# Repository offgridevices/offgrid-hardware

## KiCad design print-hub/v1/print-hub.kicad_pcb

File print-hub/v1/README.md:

# Print Hub — v1

**Five switched USB ports for a resin printer's accessories**, controlled
by the print server. The exhaust fan, the light and the air filters plug
into the board; when a print starts, the server tells the board which ports
to switch on, and later which to switch off (and when). Each port measures
its own current, limits it, and can never put more than 5.4 V on a device.
The board talks Wi-Fi, and has a USB-C port for the server too.

> **Status: designed, not yet built.** Routed 4-layer board, 86 × 50 mm,
> every track corner at 45 degrees, KiCad 10 DRC 0 errors, 0 warnings,
> 0 unconnected; every gate, design check and simulation in `TESTS.md`
> passes, the board's heat in its closed case included; firmware builds and
> its logic passes its tests on the host. Nothing has been measured on hardware: order a few,
> bring one up (below), then use it.

## This revision

| | |
|---|---|
| Revision | **v1** (product: [`../README.md`](../README.md)) |
| Status | designed, not yet built |
| Tests and simulations | [`TESTS.md`](TESTS.md): every one with its v1 result |
| Trade-offs | [`docs/decisions.md`](docs/decisions.md) |
| Parts, stock, second sources | [`docs/parts.md`](docs/parts.md) (read 17 Oct 2026) |
| Toolchain | KiCad 10.0.6 (pinned image, `tools/Dockerfile`), Freerouting 1.9.0, ngspice |
| Firmware | ESP32-S3, Arduino core 3.3.12 (pioarduino 55.03.312-1), `firmware/` |
| Brand | OffGrid v3.2.2 ([`docs/brand.md`](../../docs/brand.md)) |

## Requirements

As the owner set them, and where v1 stands.

| Requirement | v1 |
|---|---|
| One USB-ish box behind the printer that switches the accessories automatically | ✅ 5 switched USB-A ports, commands from the print server |
| 4 ports, 5 if possible | ✅ 5 |
| Controlled from the Dell over USB, or Wi-Fi | ✅ both: Wi-Fi (HTTP, `printhub.local`) and USB-C to the server, same commands |
| Easy to configure from an SSH session ("port 1 is the fan") | ✅ `printhub name 1 fan`; names, limits and priorities live on the board |
| Never burns anything out | ✅ each port's switch limits at 1.92-2.20 A and shuts down when hot; a 1.5 A software limit per port; 5.4 V output clamp; 3 A for all ports together, and a thermistor by the buck: the firmware turns ports down before any part passes its rating (`sim/thermal/board_heat.md`) |
| Never browns out the other electronics | ✅ a short on one port leaves the others above 4.75 V (`sim/port_events.md`); the firmware keeps the total under what the charger offers; the server's USB never feeds a port |
| Knows how much power it can give | ✅ reads the charger's USB-PD contract and budgets the ports from it |
| Powered from the Dell alone if possible | ⚠️ the logic yes; the accessories need about 15 W, three times what a PC USB port gives, so the ports need a USB-C charger (20 W or more) — `docs/decisions.md` |
| Relay or something reliable | ✅ solid-state USB power switches (TI TPS25200): silent, no wear |
| Not too big, not too expensive | ✅ 86 × 50 mm (under 100 mm a side: JLCPCB's $8 price for five 4-layer boards); about $11.50 of parts a board plus JLCPCB's fees (see *Ordering*) |
| Order fully assembled | ✅ JLCPCB: every part from its catalogue, BOM and CPL in `production/` |
| A 3D-printable enclosure the board screws into | ✅ `mechanical/enclosure/` |

## Next steps

1. **Order 2-5 boards** (see *Ordering*). Re-read stock first
   (`python3 tools/lcsc.py C2913198 ...`): `docs/parts.md` is dated.
2. **Print the enclosure** (`mechanical/enclosure/README.md`) and buy the
   screws, a USB-C PD charger (20 W or more) and two USB-C cables.
3. **Bring one up** (below): flash, join Wi-Fi, name the ports, load-test
   each port against a USB meter.
4. **Wire it into the print server's start/end hooks**
   (`host/examples/print-hooks.sh`).
5. **Record what the board measured** in `TESTS.md` (the hardware rows).

---

## What's on the board

- **POWER IN (USB-C, back left).** A Hynetek HUSB238 asks the charger for
  9 V over USB-PD; a Silergy SY8368A buck makes 5.16 V for the ports (rated
  5 A; the firmware allows 3 A, what the closed case can shed). A 15 V TVS
  on the input, and a thermistor between the buck and its inductor, the
  hottest corner.
- **DATA (USB-C, back middle).** Straight to the ESP32-S3's own USB (serial
  console and flashing), ESD-protected. It powers the logic, never the ports.
- **ESP32-S3-WROOM-1 (back right)**, its antenna at the board's edge with no
  copper under it. RESET and BOOT buttons and the status LED beside it.
- **Five port blocks (front)**, one per USB-A: a TI TPS25200 switch (current
  limit 2.07 A typical, soft start, fault line, 5.4 V output clamp), a
  20 mOhm shunt and a TI INA180A2 amplifier (1 V per A into the ESP32's
  ADC), and an RGB LED. D+ and D- are joined (a USB charging port), so
  devices may draw 1.5 A.
- **LEDs**: one per port (green on, blue about to come on, blinking red
  tripped, amber off for lack of power or heat) and a status LED (green on
  Wi-Fi, blinking blue in setup mode, blinking red with no USB-PD charger,
  amber while heat is turning the ports down, fast red blink when heat has
  switched them all off).
- **Test pads**: UART TX/RX and ground (boot log), and the 5 V rail.

| | |
|---|---|
| Size | 86 × 50 mm, 1.6 mm, square corners, 2 × M3 holes at (-39.5, -21.5) and (7.0, -2.5) mm from the centre (the USB-A ports hold the front edge in the case) |
| PCB | 4 layers (F signals, In1 ground, In2 5 V plane, B signals), 1 oz outer, 0.15 mm track and gap, 0.6 / 0.3 mm vias, every track corner 45 degrees or less: JLCPCB's standard tier |
| Input | USB-C PD, 9 V (asks for 9 V; 5 V-only chargers run the logic but no ports) |
| Ports | 5 × USB-A 17 mm apart, 5.16 V, 1.5 A each (the USB-A receptacles' rating; less if set), 3 A in total (2.7 A on a plain 20 W charger), less if the board gets hot |
| Control | Wi-Fi 2.4 GHz (HTTP API, mDNS `printhub.local`), USB serial |

## Ordering (JLCPCB)

From `production/`:

- **Gerbers**: `print-hub-gerbers.zip`.
- **4 layers, 1.6 mm, 1 oz outer / 0.5 oz inner** (JLC04161H-7628).
- **Green solder mask, white silkscreen, lead-free HASL**: the cheapest
  build. Black mask adds $8 and ENIG $17 per order of five (live quotes,
  18 Oct 2026); either works if wanted.
- No special options: no via-in-pad, no fine-line, no impedance control.
- **Assembly: top side only**: upload `print-hub-bom-jlcpcb.csv` and
  `print-hub-cpl-jlcpcb.csv`. Try "Economic PCBA" first: with a green mask
  the board qualifies, and JLCPCB's capability page now lists through-hole
  parts (the five USB-A) for it, which saves about $40 of setup. If the
  quote refuses, use "Standard PCBA".
- **Check before you pay**, in JLCPCB's placement preview: the pin-1 corner
  of the six WS2812B LEDs, the bands of the two B5819W diodes (D2, D3) and
  of the SMAJ15A (D1), and that the USB-C and USB-A connectors face off the
  board edge.

PCBWay: `print-hub-bom-pcbway.csv` carries manufacturer part numbers and
LCSC numbers.

**Cost, roughly** (18 Oct 2026, 5 boards): the PCB $8 (4 layers, green,
HASL, under 100 × 100 mm; the first 104 × 66 mm layout quoted $29); parts
about $11.50 a board; 14 extended + 2 preferred-extended part types at about
$3 each, so about $45 of setup fees per order; plus assembly setup and the
through-hole soldering. Ten boards halve the fees per board. Read the quote.

**Also buy:** a USB-C PD charger, 20 W or more (any phone or laptop one);
a USB-C cable for power and a USB-C to USB-A (or C) cable to the server;
M3 screws and inserts for the enclosure (its README has the list).

## Bring-up

1. **Before power**: look for solder bridges on the USB-C pins and the ESP32
   module.
2. **DATA only (no charger)**: plug DATA into the print server. The status
   LED blinks red (no charger, which is expected). `ls /dev/ttyACM*` shows
   the board.
3. **Flash the firmware** from the server (once; later updates can go over
   Wi-Fi):
   ```
   pip install esptool
   esptool --chip esp32s3 --port /dev/ttyACM0 write-flash 0x0 firmware/release/printhub-v1.1.0-factory.bin
   ```
   If esptool cannot connect: hold BOOT, press and release RESET, release
   BOOT, and run it again. Or build and flash from source:
   `cd firmware && pio run -t upload`.
4. **Install the command** on the server: `sudo cp host/printhub.py
   /usr/local/bin/printhub` (Python 3, nothing else to install).
5. **Join Wi-Fi** over the cable: `printhub wifi "Network name" "password"`,
   then `printhub status` shows its address. Optionally `printhub token
   SECRET` and `export PRINTHUB_TOKEN=SECRET` on the server.
6. **Plug in the charger** (POWER IN): the status LED turns green, and
   `printhub status` shows `9V ... USB-PD` and how many mA the ports may draw.
7. **Name the ports and test each one** with a USB load or a USB meter:
   ```
   printhub name 1 fan
   printhub name 2 light
   printhub name 3 filter1
   printhub name 4 filter2
   printhub priority fan 1
   printhub on fan          # LED goes green; status shows the current
   printhub off fan
   ```
   Check each port's reading against the meter, and that 5 V reaches the
   device (4.9-5.2 V).
8. **Hook it to the print server** (`host/examples/print-hooks.sh`):
   `printhub on fan light filter1 filter2` when a print starts;
   `printhub off fan after 15m`, `printhub off light after 3m`,
   `printhub off filter1 filter2 after 30m` when it ends. The timers run
   on the board, so they happen even if the server restarts.

The air filters: their own power button has to be pressed for them to run,
so wire it permanently on (the plan), and switching the port then decides
whether they run on charge.

## Controlling it

Home Assistant: [`docs/home-assistant.md`](docs/home-assistant.md) has the
switches and sensors ready to paste.

Over Wi-Fi: `http://printhub.local/` is a small page with the five ports
and on/off buttons. Scripts and AI agents use the same commands as the CLI,
by `printhub ...` or `POST /api/cmd` with the command as the body, and get
JSON back (`firmware/lib/hub/src/cmd.h` lists every command):

```
printhub status                     printhub on fan light [for 10m]
printhub off all                    printhub off fan after 15m
printhub name 3 filter1             printhub limit filter1 1200
printhub priority fan 1             printhub boot light on
printhub --json status              printhub ota http://server/printhub.bin
```

## Limits

- **The ports need a USB-PD charger that offers 9 V** (practically every
  USB-C charger of 18 W or more). A 5 V-only charger runs the board but no
  ports; the firmware says so. Budget by charger: 20 W gives the ports
  2.7-3.0 A, 27 W and up the full 3 A (`sim/power_budget.md`).
- **1.5 A per port at most** (the USB-A receptacles' rating; the switch's own limit is
  1.92-2.20 A); **3 A in total**: what the closed case sheds in a 35 C room
  with every part inside its rating (`sim/thermal/board_heat.md`). The
  typical load, fan + light + two filters charging, is about 2.65 A.
- **Heat**: hotter than that (a hotter room, the case in the sun, its feet or
  vents blocked), the thermistor by the buck turns the ports down from
  74 C on the board (down to 1 A by 77 C), lowest priority first, and switches them all off at
  80 C until the board is back under 70 C. `printhub status` shows the
  board's temperature.
- **2.4 GHz Wi-Fi only.** Keep metal and the screws away from the antenna
  corner; the enclosure does.
- **Power-only USB ports**: no data reaches the accessories.
- **Not measured on hardware yet**: the buck's feed-forward capacitor (22 pF)
  and the 1.5 A software limit are first guesses to confirm on the bench.

## Build

Everything runs in the pinned toolchain image. Build it once (the
Dockerfile's header says how), then from this folder:

```
tools/kd python3 src/make.py              # gates and every output from the committed board
tools/kd python3 src/make.py --artwork    # lay the silkscreen out again first
tools/kd python3 src/make.py --reroute    # place and route from scratch, then everything
tools/kd python3 src/verify.py            # design checks, writes VERIFICATION.md
tools/kd python3 sim/port_events.py       # ngspice: ports switching on, a port shorted
tools/kd python3 sim/thermal/board_heat.py  # the board's heat in its case (~5 min)
python3 sim/power_budget.py               # the power chain from the datasheets
make -C firmware/test                     # firmware logic, on the host
python3 host/test_printhub.py             # the CLI against a fake board
cd firmware && pio run                    # the firmware
```

The committed `print-hub.kicad_pcb` is the design of record: CI (`ci /
print-hub-v1`) rebuilds the artwork and every fab file from it and fails
if they differ from what is committed. `make.py --reroute` reproduces it
from `src/` (placement, power copper and Freerouting are deterministic).

| To change | Edit | Then run |
|---|---|---|
| A part number (same footprint) | `src/parts.py` | `make.py` |
| Labels, logo | `src/silk.py` | `make.py --artwork` |
| Connections, placement, power copper | `src/circuit.py`, `src/layout.py`, `src/power.py` | a new revision: copy to `v2/`, `make.py --reroute` |
| Firmware pins or scaling | `firmware/src/board.h` (must match `src/circuit.py`) | `verify.py` |

## Files

```
README.md               this file
TESTS.md                every test and simulation with its v1 result
VERIFICATION.md         design checks (src/verify.py)
print-hub.kicad_pcb     the routed board (design of record), .kicad_pro, .kicad_dru
production/             Gerber zip, BOM and CPL (JLCPCB, PCBWay), netlist, assembly PDF
images/                 renders and the silkscreen read back from the Gerbers
mechanical/             STEP of the assembled board (zipped); enclosure/
firmware/               ESP32-S3 firmware (PlatformIO), host tests, ready-to-flash images
host/                   printhub command for the print server, its tests, example hooks
docs/                   decisions, parts (dated), Home Assistant
sim/                    power-chain analysis, ngspice port events, the board's heat in its case
src/                    the generator: circuit, footprints, placement, power copper, routing, artwork, checks
ph.pretty/, ph.3dshapes/  this board's footprints and their 3D models
fonts/                  brand fonts for the silkscreen (OFL)
tools/                  pinned toolchain (Docker), CI output check, JLCPCB stock lookup
```

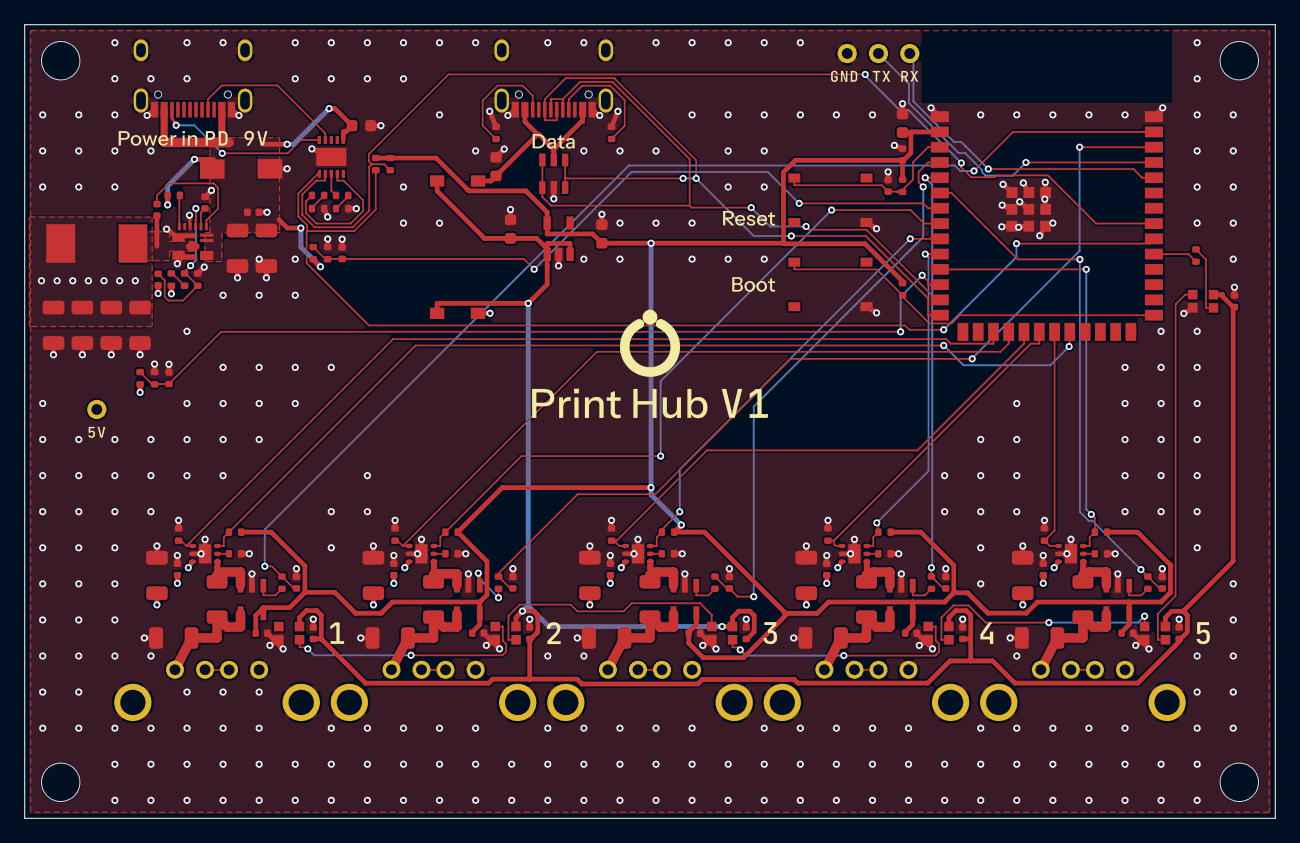
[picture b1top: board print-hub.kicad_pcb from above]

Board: 4 copper layers, 104.0 x 66.0 mm, 136 parts (0 on the bottom side), 77 nets.

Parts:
C1: 1uF; C_0603_1608Metric
C2, C3: 10uF; C_1206_3216Metric
C4, C5, C12, C13, C18, C20, C101, C103, C104, C106, C201, C203, C204, C206, C301, C303, C304, C306, C401, C403, C404, C406, C501, C503, C504, C506: 100nF; C_0402_1005Metric
C6, C19: 1uF; C_0402_1005Metric
C7: 22pF; C_0402_1005Metric
C8, C9, C10, C11, C102, C105, C202, C205, C302, C305, C402, C405, C502, C505: 22uF; C_1206_3216Metric
C14, C15, C16: 10uF; C_0603_1608Metric
C17: 22uF; C_0603_1608Metric
D1: SMAJ15A; SMA_L4.3-W2.6-LS5.0-RD
D2, D3: B5819W; SOD-123_L2.7-W1.6-LS3.7-RD-1
H1, H2, H3, H4: HOLE; MOUNT_M3
J1, J2: USB-C; USB-C_SMD-TYPE-C-31-M-12_1
J101, J201, J301, J401, J501: USB-A; USB-A-TH__USB-AF-90
L1: 2.2uH; IND-SMD_L7.0-W6.6
LED1, LED101, LED201, LED301, LED401, LED501: WS2812B-2020; LED-SMD_4P-L2.2-W2.0-P1.00_WS2815C-2020-4P
R1, R15, R16: 5.1k; R_0402_1005Metric
R2, R9, R105, R205, R305, R405, R505: 1k; R_0402_1005Metric
R3, R10, R17, R18, R103, R203, R303, R403, R503: 10k; R_0402_1005Metric
R4: 470R; R_0402_1005Metric
R5, R6: 4.7k; R_0402_1005Metric
R7, R11, R13, R14, R102, R202, R302, R402, R502: 100k; R_0402_1005Metric
R8: 75k; R_0402_1005Metric
R12: 15k; R_0402_1005Metric
R19: 100R; R_0402_1005Metric
R101, R201, R301, R401, R501: 47k; R_0402_1005Metric
R104, R204, R304, R404, R504: 20mR; R_1206_3216Metric
SW1, SW2: button; SW-SMD_4P-L5.1-W5.1-P3.70-LS6.5-TL_H1.5
TP1, TP2, TP3, TP4: TP; PAD_TP
U1: HUSB238; DFN-10_L3.0-W3.0-P0.50-BL-EP2.5
U2: SY8368A; QFN-12_L3.0-W3.0-P0.45-TL-EP
U3: USBLC6-2SC6; SOT-23-6_L2.9-W1.6-P0.95-LS2.8-BL
U4: AP2112K-3.3; SOT-25-5_L2.9-W1.6-P0.95-LS2.8-BL
U5: ESP32-S3-WROOM-1-N8; WIFIM-SMD_ESP32-S3-WROOM-1-N8
U101, U201, U301, U401, U501: TPS25200; WSON-6_L2.0-W2.0-P0.65-TL-EP
U102, U202, U302, U402, U502: INA180A2; SOT-23-5_L3.0-W1.7-P0.95-LS2.8-BL

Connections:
+3V3: C16.1, C17.1, C18.1, C103.1, C203.1, C303.1, C403.1, C503.1, R5.2, R6.2, R17.2, R18.2, R103.2, R203.2, R303.2, R403.2, R503.2, U4.5, U5.2, U102.5, U202.5, U302.5, U402.5, U502.5
BOOT: R18.1, SW2.1, U5.27
BUCK_BS: C5.1, U2.7
BUCK_EN: R7.2, U2.12
BUCK_FB: C7.2, R9.2, R10.1, U2.9
BUCK_FB2: R8.2, R9.1
BUCK_LX: C5.2, L1.1, U2.2
BUCK_VCC: C6.1, U2.8
CC1_DATA: J2.A5, R15.1
CC1_IN: J1.A5, U1.4
CC2_DATA: J2.B5, R16.1
CC2_IN: J1.B5, U1.5
DCP1: J101.2, J101.3
DCP2: J201.2, J201.3
DCP3: J301.2, J301.3
DCP4: J401.2, J401.3
DCP5: J501.2, J501.3
EN1: R102.1, U5.17, U101.4
EN2: R202.1, U5.18, U201.4
EN3: R302.1, U5.19, U301.4
EN4: R402.1, U5.20, U401.4
EN5: R502.1, U5.21, U501.4
ESP_EN: C19.1, R17.1, SW1.1, U5.3
FLT1: R103.1, U5.22, U101.3
FLT2: R203.1, U5.8, U201.3
FLT3: R303.1, U5.9, U301.3
FLT4: R403.1, U5.10, U401.3
FLT5: R503.1, U5.11, U501.3
GND: C1.2, C2.2, C3.2, C4.2, C6.2, C8.2, C9.2, C10.2, C11.2, C12.2, C13.2, C14.2, C15.2, C16.2, C17.2, C18.2, C19.2, C20.2, C101.2, C102.2, C103.2, C104.2, C105.2, C106.2, C201.2, C202.2, C203.2, C204.2, C205.2, C206.2, C301.2, C302.2, C303.2, C304.2, C305.2, C306.2, C401.2, C402.2, C403.2, C404.2, C405.2, C406.2, C501.2, C502.2, C503.2, C504.2, C505.2, C506.2, D1.2, J1.1, J1.2, J1.3, J1.4, J1.A1B12, J1.B1A12, J2.1, J2.2, J2.3, J2.4, J2.A1B12, J2.B1A12, J101.4, J101.SH1, J101.SH2, J201.4, J201.SH1, J201.SH2, J301.4, J301.SH1, J301.SH2, J401.4, J401.SH1, J401.SH2, J501.4, J501.SH1, J501.SH2, LED1.2, LED101.2, LED201.2, LED301.2, LED401.2, LED501.2, R2.2, R4.2, R10.2, R12.2, R14.2, R15.2, R16.2, R101.2, R102.2, R201.2, R202.2, R301.2, R302.2, R401.2, R402.2, R501.2, R502.2, SW1.4, SW2.4, TP3.1, U1.11, U2.1, U2.3, U2.10, U3.2, U4.2, U5.1, U5.40, U5.41, U101.5, U101.7, U102.2, U201.5, U201.7, U202.2, U301.5, U301.7, U302.2, U401.5, U401.7, U402.2, U501.5, U501.7, U502.2
ILIM1: R101.1, U101.2
ILIM2: R201.1, U201.2
ILIM3: R301.1, U301.2
ILIM4: R401.1, U401.2
ILIM5: R501.1, U501.2
IS1: C104.1, R105.2, U5.39
IS2: C204.1, R205.2, U5.38
IS3: C304.1, R305.2, U5.4
IS4: C404.1, R405.2, U5.5
IS5: C504.1, R505.2, U5.6
ISA1: R105.1, U102.1
ISA2: R205.1, U202.1
ISA3: R305.1, U302.1
ISA4: R405.1, U402.1
ISA5: R505.1, U502.1
LED_C1: LED101.3, LED201.1
LED_C2: LED201.3, LED301.1
LED_C3: LED301.3, LED401.1
LED_C4: LED401.3, LED501.1
LED_C5: LED1.1, LED501.3
LED_D0: LED1.3, R19.2
LED_DIN0: R19.1, U5.31
PD_ISET: R3.1, U1.9
PD_ISET2: R3.2, R4.1
PD_VSET: R1.1, U1.8
PD_VSET2: R1.2, R2.1
PORT1_SW: R104.1, U101.1, U102.3
PORT2_SW: R204.1, U201.1, U202.3
PORT3_SW: R304.1, U301.1, U302.3
PORT4_SW: R404.1, U401.1, U402.3
PORT5_SW: R504.1, U501.1, U502.3
RAIL_SENSE: C13.1, R13.2, R14.1, U5.12
RXD0: TP2.1, U5.36
SCL: R6.1, U1.7, U5.33
SDA: R5.1, U1.6, U5.32
TXD0: TP1.1, U5.37
USB_DN: J2.A7, J2.B7, U3.1, U3.6, U5.13
USB_DP: J2.A6, J2.B6, U3.3, U3.4, U5.14
VBUS1: C105.1, J101.1, R104.2, U102.4
VBUS2: C205.1, J201.1, R204.2, U202.4
VBUS3: C305.1, J301.1, R304.2, U302.4
VBUS4: C405.1, J401.1, R404.2, U402.4
VBUS5: C505.1, J501.1, R504.2, U502.4
VBUS_DATA: C14.1, D3.2, J2.A4B9, J2.B4A9, U3.5
VBUS_IN: C1.1, C2.1, C3.1, C4.1, D1.1, J1.A4B9, J1.B4A9, R7.1, R11.1, U1.1, U2.4, U2.5, U2.6
VIN_SENSE: C12.1, R11.2, R12.1, U5.7
VLOGIC: C15.1, C20.1, C106.1, C206.1, C306.1, C406.1, C506.1, D2.1, D3.1, LED1.4, LED101.4, LED201.4, LED301.4, LED401.4, LED501.4, U4.1, U4.3
VRAIL: C7.1, C8.1, C9.1, C10.1, C11.1, C101.1, C102.1, C201.1, C202.1, C301.1, C302.1, C401.1, C402.1, C501.1, C502.1, D2.2, L1.2, R8.1, R13.1, TP4.1, U101.6, U201.6, U301.6, U401.6, U501.6

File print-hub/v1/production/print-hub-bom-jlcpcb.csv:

Comment,Designator,Footprint,LCSC Part #
1k,"R2,R9,R105,R205,R305,R405,R505",R_0402_1005Metric,C11702
TPS25200,"U101,U201,U301,U401,U501",WSON-6_L2.0-W2.0-P0.65-TL-EP,C128401
22uF,"C8,C9,C10,C11,C102,C105,C202,C205,C302,C305,C402,C405,C502,C505",C_1206_3216Metric,C12891
10uF,"C2,C3",C_1206_3216Metric,C13585
100nF,"C5,C12,C13,C18,C20,C101,C103,C104,C106,C201,C203,C204,C206,C301,C303,C304,C306,C401,C403,C404,C406,C501,C503,C504,C506",C_0402_1005Metric,C1525
22pF,C7,C_0402_1005Metric,C1555
1uF,C1,C_0603_1608Metric,C15849
20mR,"R104,R204,R304,R404,R504",R_1206_3216Metric,C163047
USB-C,"J1,J2",USB-C_SMD-TYPE-C-31-M-12_1,C165948
2.2uH,L1,IND-SMD_L7.0-W6.6,C167218
SMAJ15A,D1,SMA_L4.3-W2.6-LS5.0-RD,C19077535
INA180A2,"U102,U202,U302,U402,U502",SOT-23-5_L3.0-W1.7-P0.95-LS2.8-BL,C192764
10uF,"C14,C15,C16",C_0603_1608Metric,C19702
SY8368A,U2,QFN-12_L3.0-W3.0-P0.45-TL-EP,C207642
USB-A,"J101,J201,J301,J401,J501",USB-A-TH__USB-AF-90,C2345
100R,R19,R_0402_1005Metric,C25076
470R,R4,R_0402_1005Metric,C25117
100k,"R7,R11,R13,R14,R102,R202,R302,R402,R502",R_0402_1005Metric,C25741
10k,"R3,R10,R17,R18,R103,R203,R303,R403,R503",R_0402_1005Metric,C25744
15k,R12,R_0402_1005Metric,C25756
47k,"R101,R201,R301,R401,R501",R_0402_1005Metric,C25792
75k,R8,R_0402_1005Metric,C25798
4.7k,"R5,R6",R_0402_1005Metric,C25900
5.1k,"R1,R15,R16",R_0402_1005Metric,C25905
ESP32-S3-WROOM-1-N8,U5,WIFIM-SMD_ESP32-S3-WROOM-1-N8,C2913198
100nF,C4,C_0402_1005Metric,C307331
button,"SW1,SW2",SW-SMD_4P-L5.1-W5.1-P3.70-LS6.5-TL_H1.5,C318884
AP2112K-3.3,U4,SOT-25-5_L2.9-W1.6-P0.95-LS2.8-BL,C51118
WS2812B-2020,"LED1,LED101,LED201,LED301,LED401,LED501",LED-SMD_4P-L2.2-W2.0-P1.00_WS2815C-2020-4P,C52917434
1uF,"C6,C19",C_0402_1005Metric,C52923
22uF,C17,C_0603_1608Metric,C59461
HUSB238,U1,DFN-10_L3.0-W3.0-P0.50-BL-EP2.5,C7471904
USBLC6-2SC6,U3,SOT-23-6_L2.9-W1.6-P0.95-LS2.8-BL,C7519
B5819W,"D2,D3",SOD-123_L2.7-W1.6-LS3.7-RD-1,C8598

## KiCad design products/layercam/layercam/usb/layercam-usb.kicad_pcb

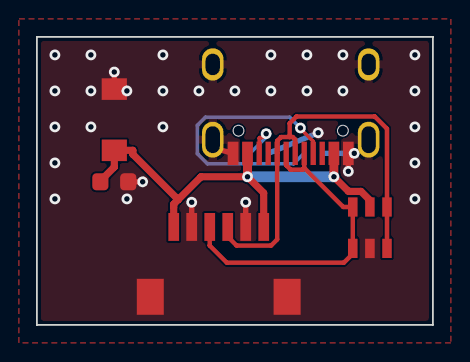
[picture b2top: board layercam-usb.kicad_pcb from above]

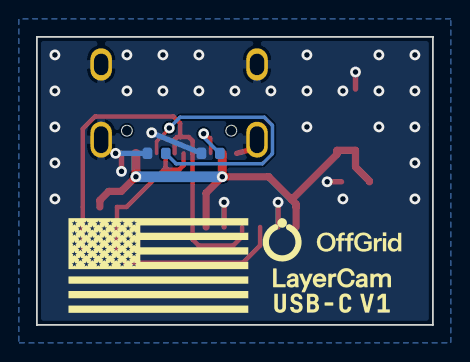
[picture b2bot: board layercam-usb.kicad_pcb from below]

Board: 2 copper layers, 22.0 x 16.0 mm, 7 parts (2 on the bottom side), 6 nets.

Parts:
C1: 10uF; C_0603_1608Metric
D1: SMF6.0CA; SOD-123FL_L2.8-W1.8-LS3.7-BI
J1: USB-C; USB-C_SMD-TYPE-C-31-M-12_1
J2: SH 6; CONN-SMD_SM06B-SRSS-TB-LF-SN
R1, R2: 5.1k; R_0402_1005Metric
U1: USBLC6-2SC6; SOT-23-6_L2.9-W1.6-P0.95-LS2.8-BL

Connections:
CC1: J1.A5, R1.1
CC2: J1.B5, R2.1
GND: C1.2, D1.2, J1.1, J1.2, J1.3, J1.4, J1.A1B12, J1.B1A12, J2.2, J2.5, J2.7, J2.8, R1.2, R2.2, U1.2
USB_DM: J1.A7, J1.B7, J2.3, U1.1, U1.6
USB_DP: J1.A6, J1.B6, J2.4, U1.3, U1.4
VSYS: C1.1, D1.1, J1.A4B9, J1.B4A9, J2.1, J2.6, U1.5

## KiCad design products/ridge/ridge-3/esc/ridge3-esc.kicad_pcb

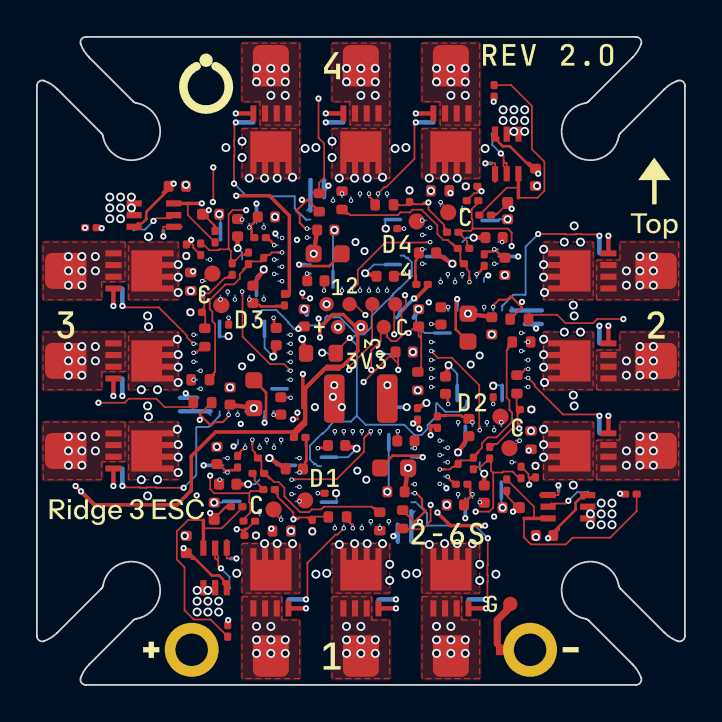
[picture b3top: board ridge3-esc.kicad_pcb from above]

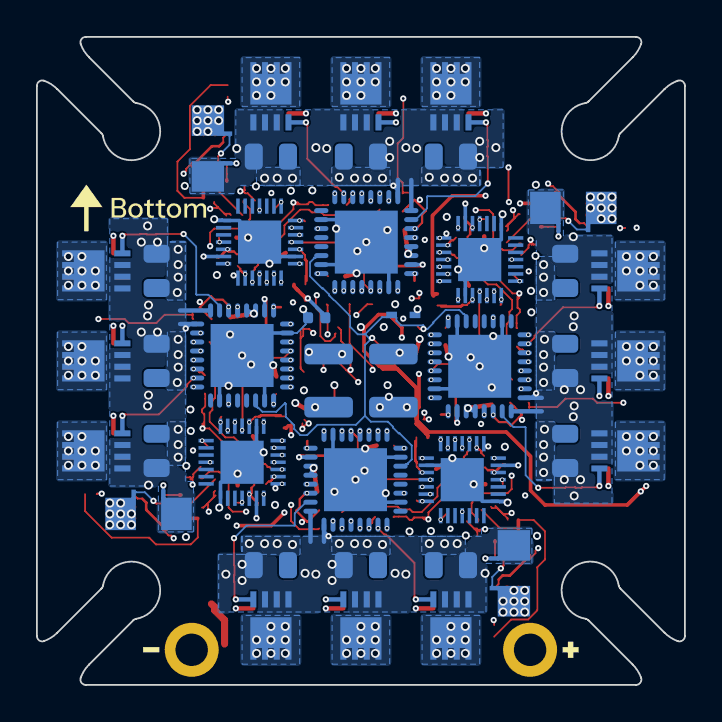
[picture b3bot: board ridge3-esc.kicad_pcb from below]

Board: 8 copper layers, 36.0 x 36.0 mm, 193 parts (40 on the bottom side), 147 nets.

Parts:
C1, C2, C3: 10uF; C_1210_3225Metric
C4, C5, C6, C7, C8, C10, C11, C18, C19, C20, C22, C23, C30, C31, C32, C34, C35, C42, C43, C44, C46, C47, C54, C55: 100nF; C_0402_1005Metric
C9, C14, C21, C26, C33, C38, C45, C50: 1uF; C_0402_1005Metric
C12, C24, C36, C48: 1uF; C_0603_1608Metric
C13, C25, C37, C49: 47nF; C_0402_1005Metric
C15, C16, C17, C27, C28, C29, C39, C40, C41, C51, C52, C53: 4.7uF; C_0805_2012Metric
D_EN: 4.7V; SOD-523_L1.2-W0.8-LS1.6-RD
FB1, FB2, FB3, FB4: 600R@100MHz; L_0201_0603Metric
H1, H2, H3, H4: HOLE; MOUNT_M2_SLOT
P_BAT+: PAD_BAT
P_BAT-: PAD_BAT_K
P_L1, P_L2, P_L3, P_L3V, P_L4: PAD_LEAD
P_LC: PAD_LEAD
P_LG: PAD_LEAD
P_LV: PAD_LEAD
P_M1A, P_M1B, P_M1C, P_M2A, P_M2B, P_M2C, P_M3A, P_M3B, P_M3C, P_M4A, P_M4B, P_M4C: PAD_MOTOR
Q1AH, Q1AL, Q1BH, Q1BL, Q1CH, Q1CL, Q2AH, Q2AL, Q2BH, Q2BL, Q2CH, Q2CL, Q3AH, Q3AL, Q3BH, Q3BL, Q3CH, Q3CL, Q4AH, Q4AL, Q4BH, Q4BL, Q4CH, Q4CL: ISZ023N06LM6; TSDSON-8FL_L3.3-W3.3-P0.65_IFX
R1, R2, R3, R4, R7, R8, R12, R15, R18, R20, R24, R27, R30, R32, R36, R39, R42, R44, R48, R51, R54: 10k; R_0201_0603Metric
R5: 33k; R_0603_1608Metric
R6: 100k; R_0402_1005Metric
R9, R21, R33, R45: 75k; R_0201_0603Metric
R10, R13, R16, R22, R25, R28, R34, R37, R40, R46, R49, R52: 20k; R_0402_1005Metric
R11, R14, R17, R23, R26, R29, R35, R38, R41, R47, R50, R53: 2k; R_0201_0603Metric
R19, R31, R43, R55: 1k; R_0201_0603Metric
RT1, RT2, RT3, RT4: NTC 10k B3380; R_0402_1005Metric
R_SH1, R_SH2, R_SH3, R_SH4: 0.5mR; RES-SMD_1206_HCS1206
TP_E1_CLK, TP_E1_DIO, TP_E2_CLK, TP_E2_DIO, TP_E3_CLK, TP_E3_DIO, TP_E4_CLK, TP_E4_DIO: PAD_TP
U_CS1, U_CS2, U_CS3, U_CS4: INA186A3; SC-70-6_L2.0-W1.3-P0.65-LS2.1-BL
U_ESC1, U_ESC2, U_ESC3, U_ESC4: AT32F421G8U7; QFN-28_L4.0-W4.0-P0.40-TL-EP2.4
U_GD1, U_GD2, U_GD3, U_GD4: DRV8320H; QFN-32_L5.0-W5.0-P0.50-TL-EP3.5

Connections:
CUR: C4.1, P_LC.1, R1.2, R2.2, R3.2, R4.2
DRV_EN: C6.1, D_EN.1, R5.2, U_GD1.22, U_GD2.22, U_GD3.22, U_GD4.22
ESC_3V3: C5.1, FB1.1, FB2.1, FB3.1, FB4.1, P_L3V.1
ESC_VSENSE: C7.1, R6.2, R7.1, U_ESC1.8, U_ESC2.8, U_ESC3.8, U_ESC4.8
FC_GND: P_BAT-.2, P_LG.1
GND: C1.2, C2.2, C3.2, C4.2, C5.2, C6.2, C7.2, C8.2, C9.2, C10.2, C11.2, C14.2, C18.2, C19.2, C20.2, C21.2, C22.2, C23.2, C26.2, C30.2, C31.2, C32.2, C33.2, C34.2, C35.2, C38.2, C42.2, C43.2, C44.2, C45.2, C46.2, C47.2, C50.2, C54.2, C55.2, D_EN.2, P_BAT-.1, R7.2, R9.2, R11.2, R14.2, R17.2, R21.2, R23.2, R26.2, R29.2, R33.2, R35.2, R38.2, R41.2, R45.2, R47.2, R50.2, R53.2, RT1.2, RT2.2, RT3.2, RT4.2, R_SH1.2, R_SH2.2, R_SH3.2, R_SH4.2, U_CS1.1, U_CS1.2, U_CS2.1, U_CS2.2, U_CS3.1, U_CS3.2, U_CS4.1, U_CS4.2, U_ESC1.1, U_ESC1.16, U_ESC1.29, U_ESC2.1, U_ESC2.16, U_ESC2.29, U_ESC3.1, U_ESC3.16, U_ESC3.29, U_ESC4.1, U_ESC4.16, U_ESC4.29, U_GD1.18, U_GD1.23, U_GD1.31, U_GD1.33, U_GD2.18, U_GD2.23, U_GD2.31, U_GD2.33, U_GD3.18, U_GD3.23, U_GD3.31, U_GD3.33, U_GD4.18, U_GD4.23, U_GD4.31, U_GD4.33
M1_3V3: C8.1, C9.1, C18.1, FB1.2, R8.1, U_CS1.3, U_ESC1.5, U_ESC1.17
M1_A: P_M1A.1, Q1AH.1, Q1AH.2, Q1AH.3, Q1AL.5, Q1AL.6, Q1AL.7, Q1AL.8, Q1AL.9, R10.1, U_GD1.6
M1_B: P_M1B.1, Q1BH.1, Q1BH.2, Q1BH.3, Q1BL.5, Q1BL.6, Q1BL.7, Q1BL.8, Q1BL.9, R13.1, U_GD1.11
M1_C: P_M1C.1, Q1CH.1, Q1CH.2, Q1CH.3, Q1CL.5, Q1CL.6, Q1CL.7, Q1CL.8, Q1CL.9, R16.1, U_GD1.14
M1_CMP_A: R10.2, R11.1, R12.1, U_ESC1.6
M1_CMP_B: R13.2, R14.1, R15.1, U_ESC1.10
M1_CMP_C: R16.2, R17.1, R18.1, U_ESC1.11
M1_CPH: C13.1, U_GD1.1
M1_CPL: C13.2, U_GD1.32
M1_DVDD: C14.1, U_GD1.24
M1_GHA: Q1AH.4, U_GD1.5
M1_GHB: Q1BH.4, U_GD1.12
M1_GHC: Q1CH.4, U_GD1.13
M1_GLA: Q1AL.4, U_GD1.7
M1_GLB: Q1BL.4, U_GD1.10
M1_GLC: Q1CL.4, U_GD1.15
M1_HA: U_ESC1.20, U_GD1.25
M1_HB: U_ESC1.19, U_GD1.27
M1_HC: U_ESC1.18, U_GD1.29
M1_IDRIVE: R9.1, U_GD1.19
M1_IOUT: R1.1, R19.1, U_CS1.6
M1_ISENSE: C19.1, R19.2, U_ESC1.12
M1_LA: U_ESC1.15, U_GD1.26
M1_LB: U_ESC1.14, U_GD1.28
M1_LC: U_ESC1.13, U_GD1.30
M1_NEUTRAL: R12.2, R15.2, R18.2, U_ESC1.7
M1_NRST: C10.1, U_ESC1.4
M1_NTC: R8.2, RT1.1, U_ESC1.9
M1_SIG: P_L1.1, U_ESC1.25
M1_SNSN: R_SH1.4, U_CS1.5
M1_SNSP: R_SH1.3, U_CS1.4
M1_SRC: C15.2, C16.2, C17.2, Q1AL.1, Q1AL.2, Q1AL.3, Q1BL.1, Q1BL.2, Q1BL.3, Q1CL.1, Q1CL.2, Q1CL.3, R_SH1.1, U_GD1.8, U_GD1.9, U_GD1.16
M1_SWCLK: TP_E1_CLK.1, U_ESC1.22
M1_SWDIO: TP_E1_DIO.1, U_ESC1.21
M1_VCP: C12.1, U_GD1.2
M2_3V3: C20.1, C21.1, C30.1, FB2.2, R20.1, U_CS2.3, U_ESC2.5, U_ESC2.17
M2_A: P_M2A.1, Q2AH.1, Q2AH.2, Q2AH.3, Q2AL.5, Q2AL.6, Q2AL.7, Q2AL.8, Q2AL.9, R22.1, U_GD2.6
M2_B: P_M2B.1, Q2BH.1, Q2BH.2, Q2BH.3, Q2BL.5, Q2BL.6, Q2BL.7, Q2BL.8, Q2BL.9, R25.1, U_GD2.11
M2_C: P_M2C.1, Q2CH.1, Q2CH.2, Q2CH.3, Q2CL.5, Q2CL.6, Q2CL.7, Q2CL.8, Q2CL.9, R28.1, U_GD2.14
M2_CMP_A: R22.2, R23.1, R24.1, U_ESC2.6
M2_CMP_B: R25.2, R26.1, R27.1, U_ESC2.10
M2_CMP_C: R28.2, R29.1, R30.1, U_ESC2.11
M2_CPH: C25.1, U_GD2.1
M2_CPL: C25.2, U_GD2.32
M2_DVDD: C26.1, U_GD2.24
M2_GHA: Q2AH.4, U_GD2.5
M2_GHB: Q2BH.4, U_GD2.12
M2_GHC: Q2CH.4, U_GD2.13
M2_GLA: Q2AL.4, U_GD2.7
M2_GLB: Q2BL.4, U_GD2.10
M2_GLC: Q2CL.4, U_GD2.15
M2_HA: U_ESC2.20, U_GD2.25
M2_HB: U_ESC2.19, U_GD2.27
M2_HC: U_ESC2.18, U_GD2.29
M2_IDRIVE: R21.1, U_GD2.19
M2_IOUT: R2.1, R31.1, U_CS2.6
M2_ISENSE: C31.1, R31.2, U_ESC2.12
M2_LA: U_ESC2.15, U_GD2.26
M2_LB: U_ESC2.14, U_GD2.28
M2_LC: U_ESC2.13, U_GD2.30
M2_NEUTRAL: R24.2, R27.2, R30.2, U_ESC2.7
M2_NRST: C22.1, U_ESC2.4
M2_NTC: R20.2, RT2.1, U_ESC2.9
M2_SIG: P_L2.1, U_ESC2.25
M2_SNSN: R_SH2.4, U_CS2.5
M2_SNSP: R_SH2.3, U_CS2.4
M2_SRC: C27.2, C28.2, C29.2, Q2AL.1, Q2AL.2, Q2AL.3, Q2BL.1, Q2BL.2, Q2BL.3, Q2CL.1, Q2CL.2, Q2CL.3, R_SH2.1, U_GD2.8, U_GD2.9, U_GD2.16
M2_SWCLK: TP_E2_CLK.1, U_ESC2.22
M2_SWDIO: TP_E2_DIO.1, U_ESC2.21
M2_VCP: C24.1, U_GD2.2
M3_3V3: C32.1, C33.1, C42.1, FB3.2, R32.1, U_CS3.3, U_ESC3.5, U_ESC3.17
M3_A: P_M3A.1, Q3AH.1, Q3AH.2, Q3AH.3, Q3AL.5, Q3AL.6, Q3AL.7, Q3AL.8, Q3AL.9, R34.1, U_GD3.6
M3_B: P_M3B.1, Q3BH.1, Q3BH.2, Q3BH.3, Q3BL.5, Q3BL.6, Q3BL.7, Q3BL.8, Q3BL.9, R37.1, U_GD3.11
M3_C: P_M3C.1, Q3CH.1, Q3CH.2, Q3CH.3, Q3CL.5, Q3CL.6, Q3CL.7, Q3CL.8, Q3CL.9, R40.1, U_GD3.14
M3_CMP_A: R34.2, R35.1, R36.1, U_ESC3.6
M3_CMP_B: R37.2, R38.1, R39.1, U_ESC3.10
M3_CMP_C: R40.2, R41.1, R42.1, U_ESC3.11
M3_CPH: C37.1, U_GD3.1
M3_CPL: C37.2, U_GD3.32
M3_DVDD: C38.1, U_GD3.24
M3_GHA: Q3AH.4, U_GD3.5
M3_GHB: Q3BH.4, U_GD3.12
M3_GHC: Q3CH.4, U_GD3.13
M3_GLA: Q3AL.4, U_GD3.7
M3_GLB: Q3BL.4, U_GD3.10
M3_GLC: Q3CL.4, U_GD3.15
M3_HA: U_ESC3.20, U_GD3.25
M3_HB: U_ESC3.19, U_GD3.27
M3_HC: U_ESC3.18, U_GD3.29
M3_IDRIVE: R33.1, U_GD3.19
M3_IOUT: R3.1, R43.1, U_CS3.6
M3_ISENSE: C43.1, R43.2, U_ESC3.12
M3_LA: U_ESC3.15, U_GD3.26
M3_LB: U_ESC3.14, U_GD3.28
M3_LC: U_ESC3.13, U_GD3.30
M3_NEUTRAL: R36.2, R39.2, R42.2, U_ESC3.7
M3_NRST: C34.1, U_ESC3.4
M3_NTC: R32.2, RT3.1, U_ESC3.9
M3_SIG: P_L3.1, U_ESC3.25
M3_SNSN: R_SH3.4, U_CS3.5
M3_SNSP: R_SH3.3, U_CS3.4
M3_SRC: C39.2, C40.2, C41.2, Q3AL.1, Q3AL.2, Q3AL.3, Q3BL.1, Q3BL.2, Q3BL.3, Q3CL.1, Q3CL.2, Q3CL.3, R_SH3.1, U_GD3.8, U_GD3.9, U_GD3.16
M3_SWCLK: TP_E3_CLK.1, U_ESC3.22
M3_SWDIO: TP_E3_DIO.1, U_ESC3.21
M3_VCP: C36.1, U_GD3.2
M4_3V3: C44.1, C45.1, C54.1, FB4.2, R44.1, U_CS4.3, U_ESC4.5, U_ESC4.17
M4_A: P_M4A.1, Q4AH.1, Q4AH.2, Q4AH.3, Q4AL.5, Q4AL.6, Q4AL.7, Q4AL.8, Q4AL.9, R46.1, U_GD4.6
M4_B: P_M4B.1, Q4BH.1, Q4BH.2, Q4BH.3, Q4BL.5, Q4BL.6, Q4BL.7, Q4BL.8, Q4BL.9, R49.1, U_GD4.11
M4_C: P_M4C.1, Q4CH.1, Q4CH.2, Q4CH.3, Q4CL.5, Q4CL.6, Q4CL.7, Q4CL.8, Q4CL.9, R52.1, U_GD4.14
M4_CMP_A: R46.2, R47.1, R48.1, U_ESC4.6
M4_CMP_B: R49.2, R50.1, R51.1, U_ESC4.10
M4_CMP_C: R52.2, R53.1, R54.1, U_ESC4.11
M4_CPH: C49.1, U_GD4.1
M4_CPL: C49.2, U_GD4.32
M4_DVDD: C50.1, U_GD4.24
M4_GHA: Q4AH.4, U_GD4.5
M4_GHB: Q4BH.4, U_GD4.12
M4_GHC: Q4CH.4, U_GD4.13
M4_GLA: Q4AL.4, U_GD4.7
M4_GLB: Q4BL.4, U_GD4.10
M4_GLC: Q4CL.4, U_GD4.15
M4_HA: U_ESC4.20, U_GD4.25
M4_HB: U_ESC4.19, U_GD4.27
M4_HC: U_ESC4.18, U_GD4.29
M4_IDRIVE: R45.1, U_GD4.19
M4_IOUT: R4.1, R55.1, U_CS4.6
M4_ISENSE: C55.1, R55.2, U_ESC4.12
M4_LA: U_ESC4.15, U_GD4.26
M4_LB: U_ESC4.14, U_GD4.28
M4_LC: U_ESC4.13, U_GD4.30
M4_NEUTRAL: R48.2, R51.2, R54.2, U_ESC4.7
M4_NRST: C46.1, U_ESC4.4
M4_NTC: R44.2, RT4.1, U_ESC4.9
M4_SIG: P_L4.1, U_ESC4.25
M4_SNSN: R_SH4.4, U_CS4.5
M4_SNSP: R_SH4.3, U_CS4.4
M4_SRC: C51.2, C52.2, C53.2, Q4AL.1, Q4AL.2, Q4AL.3, Q4BL.1, Q4BL.2, Q4BL.3, Q4CL.1, Q4CL.2, Q4CL.3, R_SH4.1, U_GD4.8, U_GD4.9, U_GD4.16
M4_SWCLK: TP_E4_CLK.1, U_ESC4.22
M4_SWDIO: TP_E4_DIO.1, U_ESC4.21
M4_VCP: C48.1, U_GD4.2
VBAT: C1.1, C2.1, C3.1, C11.1, C12.2, C15.1, C16.1, C17.1, C23.1, C24.2, C27.1, C28.1, C29.1, C35.1, C36.2, C39.1, C40.1, C41.1, C47.1, C48.2, C51.1, C52.1, C53.1, P_BAT+.1, P_LV.1, Q1AH.5, Q1AH.6, Q1AH.7, Q1AH.8, Q1AH.9, Q1BH.5, Q1BH.6, Q1BH.7, Q1BH.8, Q1BH.9, Q1CH.5, Q1CH.6, Q1CH.7, Q1CH.8, Q1CH.9, Q2AH.5, Q2AH.6, Q2AH.7, Q2AH.8, Q2AH.9, Q2BH.5, Q2BH.6, Q2BH.7, Q2BH.8, Q2BH.9, Q2CH.5, Q2CH.6, Q2CH.7, Q2CH.8, Q2CH.9, Q3AH.5, Q3AH.6, Q3AH.7, Q3AH.8, Q3AH.9, Q3BH.5, Q3BH.6, Q3BH.7, Q3BH.8, Q3BH.9, Q3CH.5, Q3CH.6, Q3CH.7, Q3CH.8, Q3CH.9, Q4AH.5, Q4AH.6, Q4AH.7, Q4AH.8, Q4AH.9, Q4BH.5, Q4BH.6, Q4BH.7, Q4BH.8, Q4BH.9, Q4CH.5, Q4CH.6, Q4CH.7, Q4CH.8, Q4CH.9, R5.1, R6.1, U_GD1.3, U_GD1.4, U_GD2.3, U_GD2.4, U_GD3.3, U_GD3.4, U_GD4.3, U_GD4.4

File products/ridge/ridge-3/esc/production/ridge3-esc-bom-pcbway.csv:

Item #,Designator,Qty,Manufacturer Part Number,Description,Value,Package/Footprint,Type,LCSC Part #,Side
1,"R1,R2,R3,R4,R7,R8,R12,R15,R18,R20,R24,R27,R30,R32,R36,R39,R42,R44,R48,R51,R54",21,RC0201FR-0710KL,Resistor 10k 1% 0201,10k,R_0201_0603Metric,SMD,C106225,Top
2,R5,1,RC0603FR-0733KL,"Resistor 33k 1% 0603, 100 mW 75 V",33k,R_0603_1608Metric,SMD,C126359,Top
3,"R19,R31,R43,R55",4,RC0201FR-071KL,Resistor 1k 1% 0201,1k,R_0201_0603Metric,SMD,C138165,Top
4,"U_CS1,U_CS2,U_CS3,U_CS4",4,INA186A3IDCKR,"Current-sense amp 100 V/V, SC-70-6",INA186A3,SC-70-6_L2.0-W1.3-P0.65-LS2.1-BL,SMD,C2058245,Top
5,D_EN,1,EDZVT2R4.7B,"Zener 4.7 V 150 mW, SOD-523",4.7V,SOD-523_L1.2-W0.8-LS1.6-RD,SMD,C209619,Bottom
6,"RT1,RT2,RT3,RT4",4,NCU15XH103F60RC,NTC thermistor 10k 1% B3380 0402,NTC 10k B3380,R_0402_1005Metric,SMD,C237326,Top
7,R6,1,0402WGF1003TCE,Resistor 100k 1% 0402,100k,R_0402_1005Metric,SMD,C25741,Top
8,"R10,R13,R16,R22,R25,R28,R34,R37,R40,R46,R49,R52",12,0402WGF2002TCE,Resistor 20k 1% 0402,20k,R_0402_1005Metric,SMD,C25765,Top
9,"U_ESC1,U_ESC2,U_ESC3,U_ESC4",4,AT32F421G8U7,"ESC MCU Cortex-M4 120 MHz 64 KB, -40..105 C (TJ 125 C), QFN-28 4x4",AT32F421G8U7,QFN-28_L4.0-W4.0-P0.40-TL-EP2.4,SMD,C2765098,Bottom
10,"R9,R21,R33,R45",4,RC0201FR-0775KL,Resistor 75k 1% 0201,75k,R_0201_0603Metric,SMD,C295816,Top
11,"C4,C5,C6,C7,C8,C10,C11,C18,C19,C20,C22,C23,C30,C31,C32,C34,C35,C42,C43,C44,C46,C47,C54,C55",24,CL05B104KB54PNC,Capacitor 100nF 50V X7R 0402,100nF,C_0402_1005Metric,SMD,C307331,Bottom+Top
12,"R11,R14,R17,R23,R26,R29,R35,R38,R41,R47,R50,R53",12,RC0201FR-072KL,Resistor 2k 1% 0201,2k,R_0201_0603Metric,SMD,C327392,Top
13,"C13,C25,C37,C49",4,CGA2B3X7R1H473KT0Y0F,Capacitor 47nF 50V X7R 0402,47nF,C_0402_1005Metric,SMD,C343051,Top
14,"R_SH1,R_SH2,R_SH3,R_SH4",4,HCS1206FTL500,Current shunt 0.5 mOhm 1% 2 W 1206,0.5mR,RES-SMD_1206_HCS1206,SMD,C346511,Bottom
15,"C1,C2,C3",3,GCJ32EC71H106KA01L,Capacitor 10uF 50V X7S 1210 soft termination,10uF,C_1210_3225Metric,SMD,C437431,Bottom+Top
16,"C15,C16,C17,C27,C28,C29,C39,C40,C41,C51,C52,C53",12,GRM21BZ71H475KE15L,Capacitor 4.7uF 50V X7R 0805,4.7uF,C_0805_2012Metric,SMD,C437557,Bottom
17,"C9,C14,C21,C26,C33,C38,C45,C50",8,GRM155Z71A105KE01D,Capacitor 1uF 10V X7R 0402,1uF,C_0402_1005Metric,SMD,C528974,Top
18,"U_GD1,U_GD2,U_GD3,U_GD4",4,DRV8320HRTVR,"60 V 3-phase smart gate driver, IDRIVE by pin, WQFN-32 5x5",DRV8320H,QFN-32_L5.0-W5.0-P0.50-TL-EP3.5,SMD,C701782,Bottom
19,"C12,C24,C36,C48",4,GCM188R71E105KA64D,Capacitor 1uF 25V X7R 0603,1uF,C_0603_1608Metric,SMD,C85862,Top
20,"FB1,FB2,FB3,FB4",4,BLM03AX601SN1D,"Ferrite bead 600 Ohm at 100 MHz, 0.25 A, 0201",600R@100MHz,L_0201_0603Metric,SMD,C88953,Top
21,"Q1AH,Q1AL,Q1BH,Q1BL,Q1CH,Q1CL,Q2AH,Q2AL,Q2BH,Q2BL,Q2CH,Q2CL,Q3AH,Q3AL,Q3BH,Q3BL,Q3CH,Q3CL,Q4AH,Q4AL,Q4BH,Q4BL,Q4CH,Q4CL",24,ISZ023N06LM6ATMA1,"N-MOSFET 60 V 2.3 mOhm logic level, PG-TSDSON-8 FL 3.3x3.3",ISZ023N06LM6,TSDSON-8FL_L3.3-W3.3-P0.65_IFX,SMD,,Bottom+Top
